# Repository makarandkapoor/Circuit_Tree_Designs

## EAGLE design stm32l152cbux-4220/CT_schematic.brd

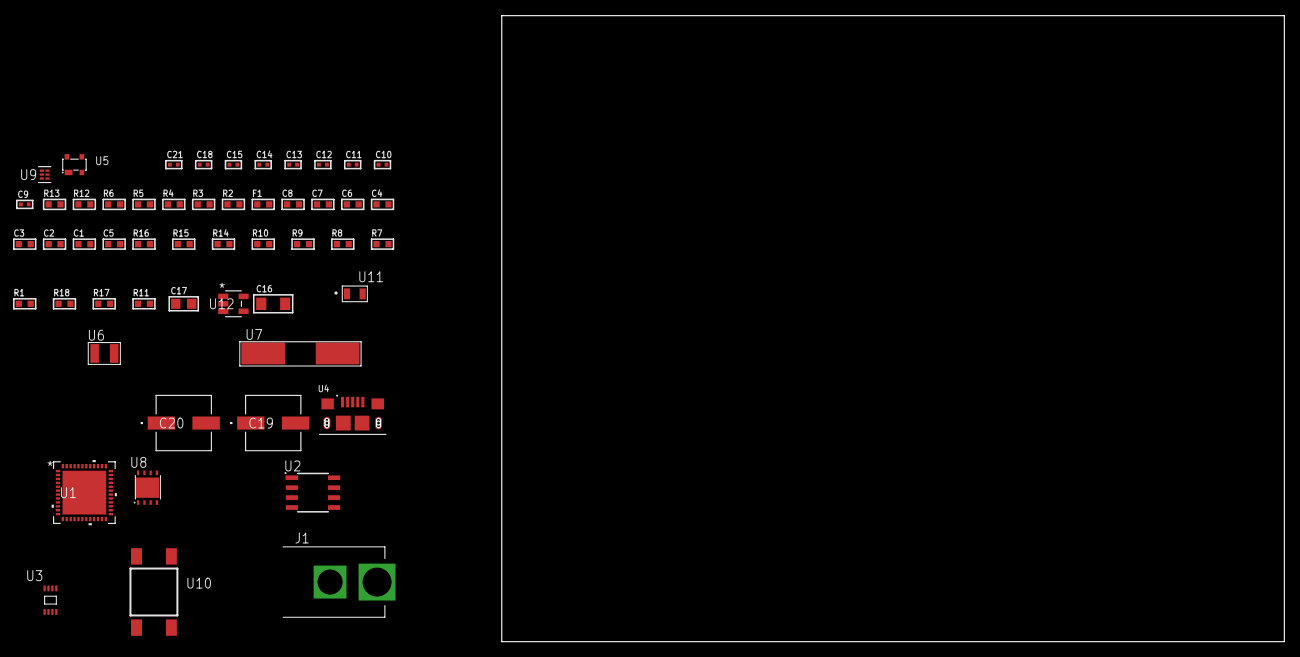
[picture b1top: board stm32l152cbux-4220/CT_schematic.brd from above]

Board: 2 copper layers, 122.6 x 80.0 mm, 53 parts (0 on the bottom side), 31 nets, no tracks yet.

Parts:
C1, C2, C3, C4, C6: 1e-07; C0603
C5: 4.7e-06; C0603
C7: 1e-08; C0603
C8: 1e-06; C0603
C9, C10, C11, C12: 1e-11; C0402
C13, C14, C15, C21: 1e-08; C0402
C16: 1e-05; C1206
C17: 1e-05; C0805
C18: 1e-07; C0402
C19, C20: 0.0001; EXV-9H
F1: 240.0; L0603
J1: PJ-037B; PJ-037B_PACKAGE
R1, R7, R8, R9, R10, R14, R15: 10000.0; R0603
R2, R13: 1000.0; R0603
R3: 910.0; R0603
R4: 4700.0; R0603
R5, R6: 2200.0; R0603
R11: 100000.0; R0603
R12: 806.0; R0603
R16: 82000.0; R0603
R17: 300000.0; R0603
R18: 120000.0; R0603
U1: STM32L152CBU6; UFQFPN48
U2: AT25128B-SSHL-T; SOIC-8
U3: 24AA16-I/MC; TDFN-8/6MM
U4: 10118193-0001LF; FCI_10118193-0001LF
U5: prtr5v0u2ax; SOT143B
U6: ABS07-32.768KHZ-7-T
U7: ABLS-25.000MHZ-B2F-T
U8: LP3878SDX-ADJ/NOPB; WSON-8
U9: TPS3895ADRYR; SON-6
U10: 4-1437565-2; SW_4-1437565-2
U11: Q65110A2395; LGM67K-G1J2-24-Z
U12: nc7sz125m5x; NC7SZ125M5X

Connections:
CLK_CRYSTAL_U1_3: C9.1, U1.3, U6.1
CLK_CRYSTAL_U1_4: C10.1, U1.4, U6.2
CLK_CRYSTAL_U1_5: C11.1, U1.5, U7.1
CLK_CRYSTAL_U1_6: C12.1, U1.6, U7.2
GND: C1.2, C2.2, C3.2, C4.2, C5.2, C6.2, C7.2, C8.2, C9.2, C10.2, C11.2, C12.2, C13.2, C14.2, C15.2, C16.2, C17.2, C18.2, C19.2, C20.2, C21.2, J1.2, R2.2, R7.2, R13.2, R16.2, R18.2, U1.8, U1.23, U1.35, U1.47, U1.49, U2.4, U3.4, U4.5, U4.6, U4.7, U4.8, U4.9, U5.1, U8.3, U8.PAD, U9.2, U11.C, U12.1, U12.3
NET_U1_1: C6.1, U1.1
NET_U1_7: R4.1, U1.7, U12.4
NET_U1_9: C7.1, C8.1, F1.1, U1.9
NET_U1_42: R5.1, U1.42, U3.6
NET_U1_43: R6.1, U1.43, U3.5
NET_U1_44: R7.1, U1.44
NET_U1_45: R3.1, U1.45, U11.A
NET_U1_46: R1.1, U1.46, U10.3, U10.4
NET_U2_3: R8.1, U2.3
NET_U2_7: R10.1, U2.7
NET_U5_4: U4.1, U5.4
NET_U8_1: C15.1, U8.1
NET_U8_6: R12.2, R13.1, U8.6
NET_U8_8: R11.1, U8.8
NET_U9_1: R15.1, R16.1, U9.1
NET_U9_3: R17.2, R18.1, U9.3
NET_U9_4: R14.1, U9.4, U12.2
NET_U10_1: R2.1, U10.1, U10.2
PROC_SPI1_MISO: U1.16, U2.2
PROC_SPI1_MOSI: U1.17, U2.5
PROC_SPI1_NSS: R9.1, U1.14, U2.1
PROC_SPI1_SCK: U1.15, U2.6
PROC_USB_DM: U1.32, U4.2, U5.3
PROC_USB_DP: U1.33, U4.3, U5.2
VCC_S1_9V1: C16.1, C19.1, C20.1, J1.1, R11.2, U8.4
VCC_TIER1_1V8: C1.1, C2.1, C3.1, C4.1, C5.1, C13.1, C14.1, C17.1, C18.1, C21.1, F1.2, R1.2, R3.2, R4.2, R5.2, R6.2, R8.2, R9.2, R10.2, R12.1, R14.2, R15.2, R17.1, U1.24, U1.36, U1.48, U2.8, U3.7, U3.8, U8.5, U9.6, U12.5

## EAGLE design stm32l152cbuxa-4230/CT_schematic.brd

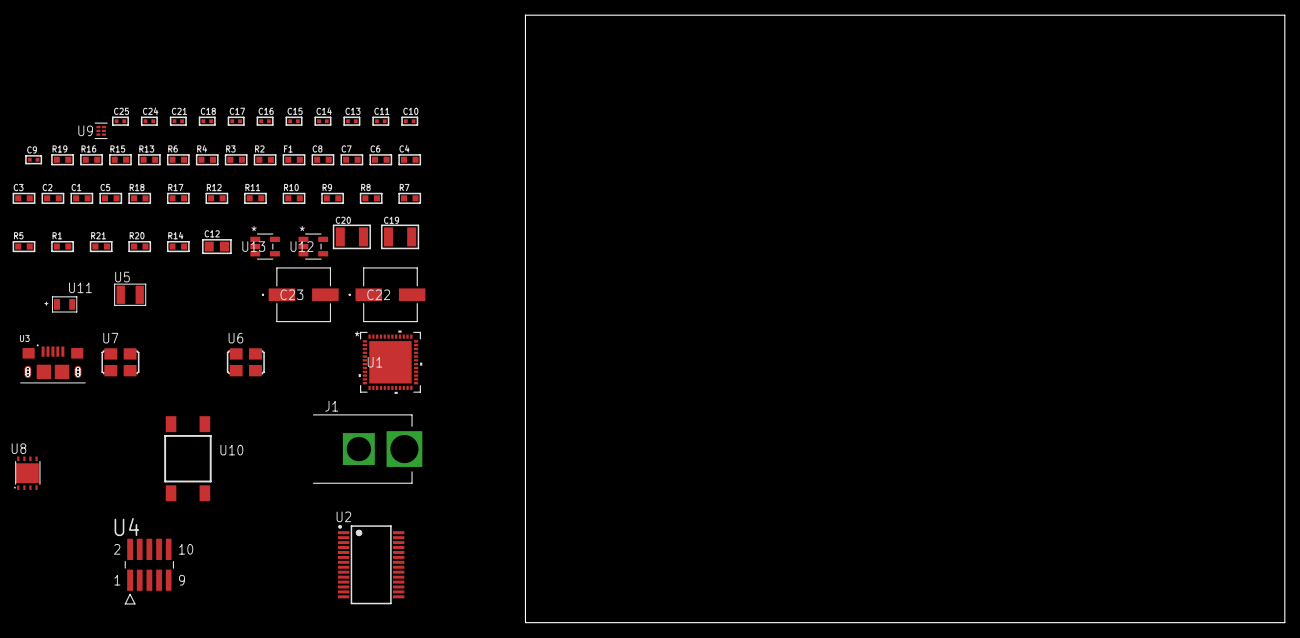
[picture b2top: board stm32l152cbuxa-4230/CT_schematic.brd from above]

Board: 2 copper layers, 165.8 x 80.0 mm, 61 parts (0 on the bottom side), 36 nets, no tracks yet.

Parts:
C1, C2, C3, C4, C6: 1e-07; C0603
C5: 4.7e-06; C0603
C7: 1e-08; C0603
C8: 1e-06; C0603
C9, C10: 1e-11; C0402
C11, C13, C14, C15, C21: 1e-07; C0402
C12: 4.7e-06; C0805
C16, C17, C18, C24, C25: 1e-08; C0402
C19, C20: 1e-05; C1210
C22, C23: 0.0001; EXV-9H
F1: 240.0; L0603
J1: PJ-037B; PJ-037B_PACKAGE
R1, R5, R7, R8, R9, R10, R11, R12, R17, R18: 10000.0; R0603
R2, R16: 1000.0; R0603
R3: 1600.5; R0603
R4, R6: 4700.0; R0603
R13: 5.0; R0603
R14: 100000.0; R0603
R15: 2231.0; R0603
R19: 9100.0; R0603
R20: 680000.0; R0603
R21: 120000.0; R0603
U1: STM32L152CBU6A; UFQFPN48
U2: FT232RL-REEL; SSOP-28
U3: 10118193-0001LF; FCI_10118193-0001LF
U4: FTSH-105-01-L-DV-K; SAMTEC_FTSH-105-01-L-DV-K
U5: ABS07-32.768KHZ-7-T
U6: ASFL1-12MHZ-NCS; ASFL1
U7: ASFL1-25MHZ-NCS; ASFL1
U8: LP3878SDX-ADJ/NOPB; WSON-8
U9: TPS3895ADRYR; SON-6
U10: 4-1437565-2; SW_4-1437565-2
U11: Q65110A2395; LGM67K-G1J2-24-Z
U12, U13: nc7sz125m5x; NC7SZ125M5X

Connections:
CLK_CRYSTAL_U1_3: C9.1, U1.3, U5.1
CLK_CRYSTAL_U1_4: C10.1, U1.4, U5.2
CLK_U1_5: U1.5, U7.3
CLK_U2_27: U2.27, U6.3
GND: C1.2, C2.2, C3.2, C4.2, C5.2, C6.2, C7.2, C8.2, C9.2, C10.2, C11.2, C12.2, C13.2, C14.2, C15.2, C16.2, C17.2, C18.2, C19.2, C20.2, C21.2, C22.2, C23.2, C24.2, C25.2, J1.2, R2.2, R5.2, R8.2, R12.2, R13.2, R16.2, R19.2, R21.2, U1.8, U1.23, U1.35, U1.47, U1.49, U2.7, U2.18, U2.21, U2.25, U2.26, U3.5, U3.6, U3.7, U3.8, U3.9, U4.3, U4.5, U6.2, U7.2, U8.3, U8.PAD, U9.2, U11.C, U12.2, U12.3, U13.1, U13.3
NET_U1_1: C6.1, U1.1
NET_U1_7: R4.1, U1.7, U13.4
NET_U1_9: C7.1, C8.1, F1.1, U1.9
NET_U1_44: R5.1, U1.44
NET_U1_45: R3.1, U1.45, U11.A
NET_U1_46: R1.1, U1.46, U10.3, U10.4
NET_U2_14: R7.1, U2.14
NET_U2_17: C13.1, U2.17
NET_U2_19: R8.1, U2.19
NET_U3_1: R6.1, U3.1
NET_U3_2: U2.16, U3.2
NET_U3_3: U2.15, U3.3
NET_U4_9: R13.1, U4.9
NET_U8_1: C18.1, U8.1
NET_U8_6: R15.2, R16.1, U8.6
NET_U8_8: R14.1, U8.8
NET_U9_1: R18.1, R19.1, U9.1
NET_U9_3: R20.2, R21.1, U9.3
NET_U9_4: R17.1, U9.4, U12.4, U13.2
NET_U10_1: R2.1, U10.1, U10.2
PROC_SYS_JTCK_SWCLK: R12.1, U1.37, U4.4
PROC_SYS_JTDI: R10.1, U1.38, U4.8
PROC_SYS_JTDO_TRACESWO: U1.39, U4.6
PROC_SYS_JTMS_SWDIO: R11.1, U1.34, U4.2
PROC_USART1_CTS: U1.32, U2.3
PROC_USART1_RTS: U1.33, U2.11
PROC_USART1_RX: U1.31, U2.1
PROC_USART1_TX: U1.30, U2.5
RST_OUT_U4_JTAG_RST_B: R9.1, U4.10, U12.1
VCC_S1_15V1: C19.1, C22.1, C23.1, J1.1, R14.2, U8.4
VCC_TIER1_3V3: C1.1, C2.1, C3.1, C4.1, C5.1, C11.1, C12.1, C14.1, C15.1, C16.1, C17.1, C20.1, C21.1, C24.1, C25.1, F1.2, R1.2, R3.2, R4.2, R7.2, R9.2, R10.2, R11.2, R15.1, R17.2, R18.2, R20.1, U1.24, U1.36, U1.48, U2.4, U2.20, U4.1, U6.4, U7.4, U8.5, U9.6, U12.5, U13.5

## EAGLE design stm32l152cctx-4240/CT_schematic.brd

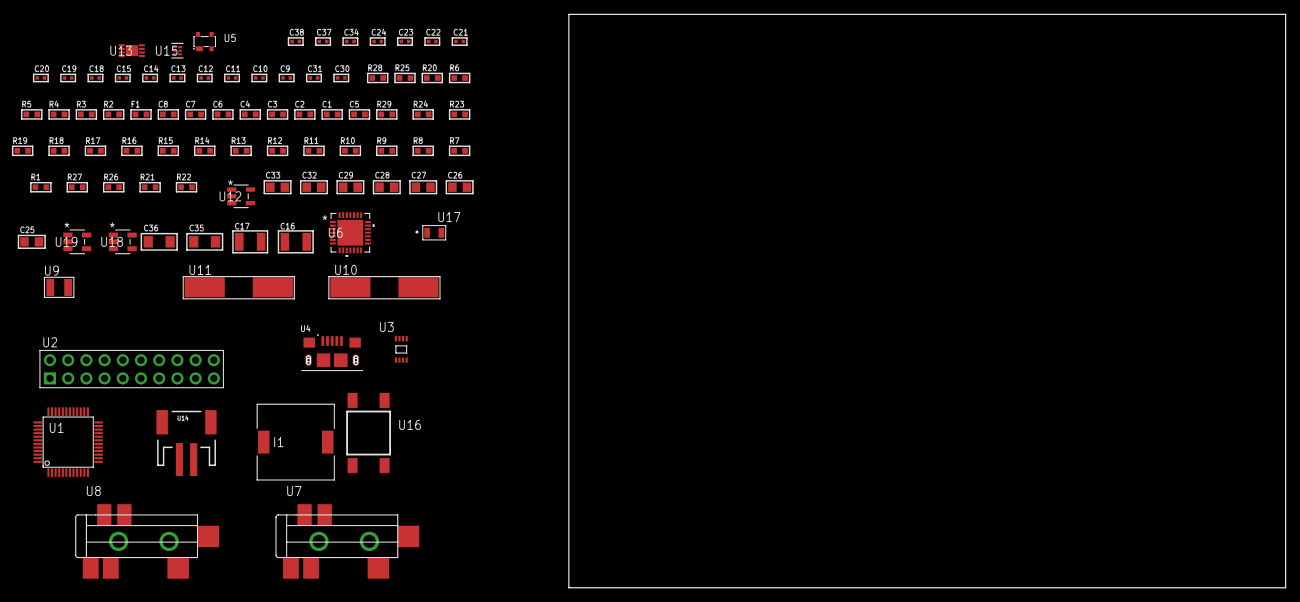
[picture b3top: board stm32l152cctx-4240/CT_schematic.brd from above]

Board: 2 copper layers, 88 parts (0 on the bottom side), 46 nets, no tracks yet.

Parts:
C1, C2, C3, C4, C6: 1e-07; C0603
C5: 4.7e-06; C0603
C7: 1e-08; C0603
C8: 1e-06; C0603
C9, C10, C11, C12: 1e-11; C0402
C13, C14, C20, C21, C22, C23, C24, C34: 1e-07; C0402
C15, C37, C38: 1e-08; C0402
C16, C17: 2.2e-05; C1210
C18, C19: 1e-09; C0402
C25, C26, C27, C28, C29, C32, C33: 1e-05; C0805
C30, C31: 2.2e-11; C0402
C35, C36: 1e-05; C1206
F1: 240.0; L0603
I1: 3.8e-06; DR1040
R1, R7, R8, R9, R10, R11, R12, R13, R14, R15, R16, R23, R24, R29: 10000.0; R0603
R2: 1000.0; R0603
R3: 1600.5; R0603
R4: 4700.0; R0603
R5, R6: 2200.0; R0603
R17, R18, R19: 47000.0; R0603
R20: 680.0; R0603
R21: 220000.0; R0603
R22: 1000000.0; R0603
R25: 9100.0; R0603
R26: 680000.0; R0603
R27: 120000.0; R0603
R28: 2000.0; R0603
U1: STM32L152CCT6; LQFP48
U2: TST-110-05-T-D-RA
U3: 24AA64T-I/MNY; TDFN-8/6MM
U4: 10118193-0001LF; FCI_10118193-0001LF
U5: prtr5v0u2ax; SOT143B
U6: WM8731CLSEFL; QFN-28
U7, U8: SJ-43515TS-SMT-TR
U9: ABS07-32.768KHZ-7-T
U10: ABLS-25.000MHZ-B2F-T
U11: ABLS-12.288MHZ-B4-T
U12: ltc3406es5; TSOT-23-5
U13: MCP73831T-2ACI/MC; DFN8_2X3MC
U14: S2B-PH-SM4-TB(LF)(SN); JST-2-SMD
U15: TPS3895ADRYR; SON-6
U16: 4-1437565-2; SW_4-1437565-2
U17: Q65110A2395; LGM67K-G1J2-24-Z
U18, U19: nc7sz125m5x; NC7SZ125M5X

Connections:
CLK_CRYSTAL_U1_3: C9.1, U1.3, U9.1
CLK_CRYSTAL_U1_4: C10.1, U1.4, U9.2
CLK_CRYSTAL_U1_5: C11.1, U1.5, U10.1
CLK_CRYSTAL_U1_6: C12.1, U1.6, U10.2
CLK_CRYSTAL_U6_1: C30.1, U6.1, U11.1
CLK_CRYSTAL_U6_2: C31.1, U6.2, U11.2
GND: C1.2, C2.2, C3.2, C4.2, C5.2, C6.2, C7.2, C8.2, C9.2, C10.2, C11.2, C12.2, C13.2, C14.2, C15.2, C19.2, C20.2, C21.2, C22.2, C23.2, C24.2, C25.2, C26.2, C27.2, C28.2, C29.2, C30.2, C31.2, C32.2, C33.1, C33.2, C34.2, C35.2, C36.2, C37.2, C38.2, R2.2, R7.2, R13.2, R15.2, R16.2, R17.2, R18.2, R19.2, R21.2, R25.2, R27.2, R28.2, U1.8, U1.23, U1.35, U1.47, U2.4, U2.6, U2.8, U2.10, U2.12, U2.14, U2.16, U2.18, U2.20, U3.4, U4.5, U4.6, U4.7, U4.8, U4.9, U5.1, U6.4, U6.15, U6.19, U6.25, U6.26, U6.29, U7.1, U8.1, U12.2, U13.6, U13.9, U14.2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
INPUT_USBPOWER_5V: C35.1, R29.2, U4.1, U5.4, U13.1, U13.2
NET_U1_1: C6.1, U1.1
NET_U1_7: R4.1, U1.7, U19.4
NET_U1_9: C7.1, C8.1, F1.1, U1.9
NET_U1_42: R5.1, U1.42, U3.6
NET_U1_43: R6.1, U1.43, U3.5
NET_U1_44: R7.1, U1.44
NET_U1_45: R3.1, U1.45, U17.A
NET_U1_46: R1.1, U1.46, U16.3, U16.4
NET_U2_19: R13.1, U2.19
NET_U3_1: R14.1, U3.1
NET_U3_2: R15.1, U3.2
NET_U3_3: R16.1, U3.3
NET_U6_20: C24.1, C29.1, U6.20
NET_U7_2: C17.1, R18.1, U7.2
NET_U7_5: C16.1, R17.1, U7.5
NET_U8_5: C18.1, C19.1, R19.1, R20.1, U8.5
NET_U12_3: I1.1, U12.3
NET_U12_5: R21.1, R22.1, U12.5
NET_U12_ATNET_3: I1.2, R22.2
NET_U13_5: R29.1, U13.5
NET_U13_8: R28.1, U13.8
NET_U15_1: R24.1, R25.1, U15.1
NET_U15_3: R26.2, R27.1, U15.3
NET_U15_4: R23.1, U15.4, U18.4, U19.2
NET_U16_1: R2.1, U16.1, U16.2
PROC_I2S2_CK: U1.26, U6.7
PROC_I2S2_SD: U1.28, U6.8
PROC_I2S2_WS: U1.25, U6.9, U6.11
PROC_SYS_JTCK_SWCLK: R11.1, U1.37, U2.9
PROC_SYS_JTDI: R9.1, U1.38, U2.5
PROC_SYS_JTDO_TRACESWO: U1.39, U2.13
PROC_SYS_JTMS_SWDIO: R10.1, U1.34, U2.7
PROC_SYS_JTRST: R8.1, U1.40, U2.3
PROC_USB_DM: U1.32, U4.2, U5.3
PROC_USB_DP: U1.33, U4.3, U5.2
RST_OUT_U2_SRESET_B: R12.1, U2.15, U18.1
VCC_S1_3V7: C32.1, C36.1, U12.4, U13.3, U13.4, U14.1
VCC_TIER1_3V3: C1.1, C2.1, C3.1, C4.1, C5.1, C13.1, C14.1, C15.1, C20.1, C21.1, C22.1, C23.1, C25.1, C26.1, C27.1, C28.1, C33.2, C34.1, C37.1, C38.1, F1.2, I1.2, R1.2, R3.2, R4.2, R5.2, R6.2, R8.2, R9.2, R10.2, R11.2, R12.2, R14.2, R22.2, R23.2, R24.2, R26.1, U1.24, U1.36, U1.48, U2.1, U2.2, U3.7, U3.8, U6.3, U6.5, U6.12, U6.18, U15.6, U18.5, U19.5

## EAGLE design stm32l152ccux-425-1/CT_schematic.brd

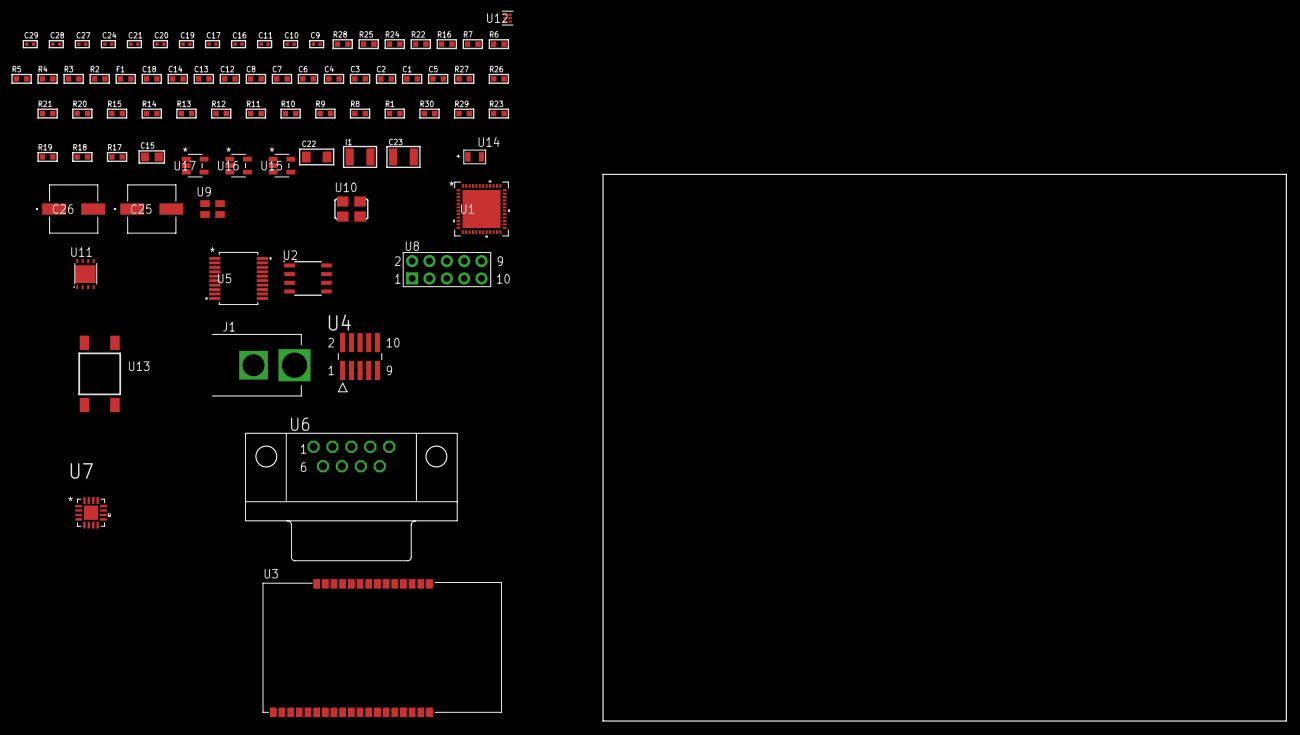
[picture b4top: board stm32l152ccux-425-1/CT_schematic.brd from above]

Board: 2 copper layers, 100.0 x 80.0 mm, 79 parts (0 on the bottom side), 60 nets, no tracks yet.

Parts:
C1, C2, C3, C4, C6: 1e-07; C0603
C5: 4.7e-06; C0603
C7: 1e-08; C0603
C8, C12, C13, C14, C18: 1e-06; C0603
C9, C19, C20, C21, C27, C28, C29: 1e-08; C0402
C10, C11, C16, C17, C24: 1e-07; C0402
C15: 4.7e-06; C0805
C22: 1e-05; C1206
C23: 1e-05; C1210
C25, C26: 0.0001; EXV-9H
F1: 240.0; L0603
I1: 1.5e-05; L1210
J1: PJ-037B; PJ-037B_PACKAGE
R1, R8, R9, R10, R11, R12, R13, R14, R15, R20, R21, R26, R27: 10000.0; R0603
R2, R25: 1000.0; R0603
R3: 1600.5; R0603
R4, R5: 4700.0; R0603
R6, R7: 2200.0; R0603
R16: 5.0; R0603
R17, R18, R19, R23: 100000.0; R0603
R22: 47.0; R0603
R24: 2231.0; R0603
R28: 9100.0; R0603
R29: 680000.0; R0603
R30: 120000.0; R0603
U1: STM32L152CCU6; UFQFPN48
U2: AT25256B-SSHL-T; SOIC-8
U3: ETRX3587
U4: FTSH-105-01-L-DV-K; SAMTEC_FTSH-105-01-L-DV-K
U5: MAX3218EAP+T; SSOP-20
U6: 182-009-113R531; 182-009-MALE
U7: TSC2013QRSARQ1; QFN65P400X400X100-17N
U8: HTSS-105-01-G-D
U9: ASEK-32.768KHz-ECST; ASEK
U10: ASFL1-25MHZ-NCS; ASFL1
U11: LP3878SDX-ADJ/NOPB; WSON-8
U12: TPS3895ADRYR; SON-6
U13: 4-1437565-2; SW_4-1437565-2
U14: Q65110A2395; LGM67K-G1J2-24-Z
U15, U16, U17: nc7sz125m5x; NC7SZ125M5X

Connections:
CLK_U1_3: U1.3, U9.3
CLK_U1_5: U1.5, U10.3
GND: C1.2, C2.2, C3.2, C4.2, C5.2, C6.2, C7.2, C8.2, C9.2, C10.2, C11.2, C12.2, C13.2, C14.2, C19.2, C20.2, C21.2, C22.2, C23.2, C24.2, C25.2, C26.2, C27.2, C28.2, C29.2, J1.2, R2.2, R8.2, R12.2, R16.2, R25.2, R28.2, R30.2, U1.8, U1.23, U1.35, U1.47, U1.49, U2.4, U3.1, U3.13, U3.19, U3.20, U3.31, U3.33, U4.3, U4.5, U5.5, U5.17, U5.20, U6.5, U7.17, U8.9, U9.2, U10.2, U11.3, U11.PAD, U12.2, U14.C, U15.2, U15.3, U16.1, U16.3, U17.1, U17.3
NET_U1_1: C6.1, U1.1
NET_U1_7: R5.1, U1.7, U17.4
NET_U1_9: C7.1, C8.1, F1.1, U1.9
NET_U1_43: R7.1, U1.43, U7.1
NET_U1_44: R8.1, U1.44
NET_U1_45: R3.1, U1.45, U14.A
NET_U1_46: R1.1, U1.46, U13.3, U13.4
NET_U2_3: R9.1, U2.3
NET_U2_7: R11.1, U2.7
NET_U3_7: R4.1, U3.7, U16.4
NET_U3_21: R12.1, U3.21
NET_U4_9: R16.1, U4.9
NET_U5_1: I1.1, U5.1
NET_U5_2: R17.1, U5.2
NET_U5_3: R18.1, U5.3
NET_U5_4: R19.1, U5.4
NET_U5_15: C14.1, U5.15
NET_U5_16: C15.2, U5.16
NET_U5_18: C15.1, U5.18
NET_U5_19: C13.1, U5.19
NET_U6_2: U5.12, U6.2
NET_U6_3: U5.14, U6.3
NET_U6_7: U5.11, U6.7
NET_U6_8: U5.13, U6.8
NET_U7_4: R21.1, U7.4
NET_U7_5: R20.1, U7.5
NET_U7_9: C16.2, C17.2, C18.2, R22.2, U7.9
NET_U7_15: R22.1, U7.8, U7.15
NET_U8_3: U7.12, U8.3
NET_U8_4: U7.14, U8.4
NET_U8_5: U7.11, U8.5
NET_U8_6: U7.13, U8.6
NET_U11_1: C21.1, U11.1
NET_U11_6: R24.2, R25.1, U11.6
NET_U11_8: R23.1, U11.8
NET_U12_1: R27.1, R28.1, U12.1
NET_U12_3: R29.2, R30.1, U12.3
NET_U12_4: R26.1, U12.4, U15.4, U16.2, U17.2
NET_U13_1: R2.1, U13.1, U13.2
PROC_SPI1_MISO: U1.16, U2.2
PROC_SPI1_MOSI: U1.17, U2.5
PROC_SPI1_NSS: R10.1, U1.14, U2.1
PROC_SPI1_SCK: U1.15, U2.6
PROC_SYS_JTCK_SWCLK: R14.1, U1.37, U4.4
PROC_SYS_JTDO_TRACESWO: U1.39, U4.6
PROC_SYS_JTMS_SWDIO: R15.1, U1.34, U4.2
PROC_USART1_CTS: U1.32, U3.8
PROC_USART1_RTS: U1.33, U3.6
PROC_USART1_RX: U1.31, U3.17
PROC_USART1_TX: U1.30, U3.18
PROC_USART2_CTS: U1.10, U5.8
PROC_USART2_RTS: U1.11, U5.10
PROC_USART2_RX: U1.13, U5.9
PROC_USART2_TX: U1.12, U5.7
RST_OUT_U4_JTAG_RST_B: R13.1, U4.10, U15.1
VCC_S1_9V7: C22.1, C25.1, C26.1, J1.1, R23.2, U11.4
VCC_TIER1_3V3: C1.1, C2.1, C3.1, C4.1, C5.1, C9.1, C10.1, C11.1, C12.1, C16.1, C17.1, C18.1, C19.1, C20.1, C23.1, C24.1, C27.1, C28.1, C29.1, F1.2, I1.2, R1.2, R3.2, R4.2, R5.2, R6.2, R7.2, R9.2, R10.2, R11.2, R13.2, R14.2, R15.2, R17.2, R18.2, R19.2, R20.2, R21.2, R24.1, R26.2, R27.2, R29.1, U1.24, U1.36, U1.48, U2.8, U3.32, U4.1, U5.6, U7.7, U7.10, U9.4, U10.4, U11.5, U12.6, U15.5, U16.5, U17.5

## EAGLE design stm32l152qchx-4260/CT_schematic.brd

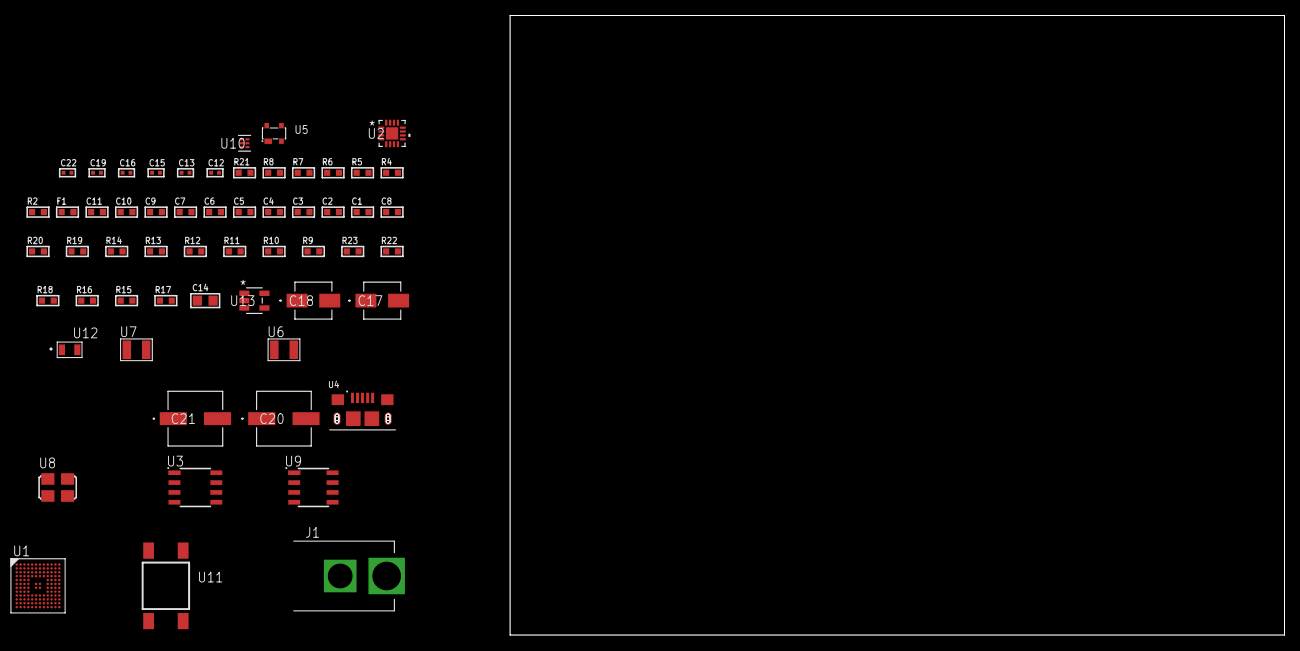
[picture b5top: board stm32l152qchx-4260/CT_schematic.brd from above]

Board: 2 copper layers, 122.6 x 80.0 mm, 58 parts (0 on the bottom side), 32 nets, no tracks yet.

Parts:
C1, C2, C3, C4, C5, C6, C7, C9: 1e-07; C0603
C8: 4.7e-06; C0603
C10: 1e-08; C0603
C11: 1e-06; C0603
C12, C13: 1e-11; C0402
C14: 4.7e-06; C0805
C15, C16, C22: 1e-08; C0402
C17: 1e-06; EXV-9B
C18: 2.2e-06; EXV-9B
C19: 1e-07; C0402
C20, C21: 0.0001; EXV-9H
F1: 240.0; L0603
J1: PJ-037B; PJ-037B_PACKAGE
R2: 1000.0; R0603
R4: 4700.0; R0603
R5, R6, R7, R8: 2200.0; R0603
R9, R10, R11, R12, R13, R14, R19, R20: 10000.0; R0603
R15, R16, R18: 100000.0; R0603
R17: 164658.62; R0603
R21: 9100.0; R0603
R22: 680000.0; R0603
R23: 120000.0; R0603
U1: STM32L152QCH6; UFBGA132
U2: M41T65Q6F; M41T65_QFN-16
U3: 24AA1025T-I/SN; SOIC-8
U4: 10118193-0001LF; FCI_10118193-0001LF
U5: prtr5v0u2ax; SOT143B
U6, U7: ABS07-32.768KHZ-7-T
U8: ASFL1-25MHZ-NCS; ASFL1
U9: LP2954AIMX/NOPB; LP2954
U10: TPS3895ADRYR; SON-6
U11: 4-1437565-2; SW_4-1437565-2
U12: Q65110A2395; LGM67K-G1J2-24-Z
U13: nc7sz125m5x; NC7SZ125M5X

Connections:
CLK_CRYSTAL_U1_D1: C12.1, U1.D1, U7.1
CLK_CRYSTAL_U1_E1: C13.1, U1.E1, U7.2
CLK_CRYSTAL_U2_1: U2.1, U6.1
CLK_CRYSTAL_U2_2: U2.2, U6.2
CLK_U1_F1: U1.F1, U8.3
GND: C1.2, C2.2, C3.2, C4.2, C5.2, C6.2, C7.2, C8.2, C9.2, C10.2, C11.2, C12.2, C13.2, C14.2, C15.2, C16.2, C17.2, C18.2, C19.2, C20.2, C21.2, C22.2, J1.2, R2.2, R9.2, R14.2, R18.2, R21.2, R23.2, U1.D3, U1.E3, U1.F2, U1.F6, U1.F7, U1.F11, U1.F12, U1.J1, U2.3, U2.5, U2.17, U3.4, U3.7, U4.5, U4.6, U4.7, U4.8, U4.9, U5.1, U8.2, U9.4, U10.2, U12.C, U13.1, U13.3
NET_U1_A3: R5.1, U1.A3, U2.10
NET_U1_A4: R9.1, U1.A4
NET_U1_B3: R6.1, U1.B3, U2.9
NET_U1_E2: C9.1, U1.E2
NET_U1_H2: R4.1, U1.H2, U13.4
NET_U1_L10: R7.1, U1.L10, U3.6
NET_U1_L11: R8.1, U1.L11, U3.5
NET_U1_M1: C10.1, C11.1, F1.1, U1.L1, U1.M1
NET_U1_M12: U11.3, U11.4
NET_U2_4: R10.1, U2.4
NET_U2_11: R11.1, U2.11
NET_U3_1: R13.1, U3.1
NET_U3_2: R14.1, U3.2
NET_U3_3: R12.1, U3.3
NET_U5_4: U4.1, U5.4
NET_U9_3: R16.1, U9.3
NET_U9_5: R15.1, U9.5
NET_U9_7: R17.2, R18.1, U9.7
NET_U10_1: R20.1, R21.1, U10.1
NET_U10_3: R22.2, R23.1, U10.3
NET_U10_4: R19.1, U10.4, U13.2
NET_U11_1: R2.1, U11.1, U11.2
PROC_USB_DM: U1.B12, U4.2, U5.3
PROC_USB_DP: U1.A12, U4.3, U5.2
VCC_S1_14V3: C17.1, C20.1, C21.1, J1.1, R16.2, U9.8
VCC_TIER1_3V3: C1.1, C2.1, C3.1, C4.1, C5.1, C6.1, C7.1, C8.1, C14.1, C15.1, C16.1, C18.1, C19.1, C22.1, F1.2, R4.2, R5.2, R6.2, R7.2, R8.2, R10.2, R11.2, R12.2, R13.2, R15.2, R17.1, R19.2, R20.2, R22.1, U1.C4, U1.G2, U1.G6, U1.G7, U1.G11, U1.G12, U1.H3, U2.14, U3.8, U8.4, U9.1, U10.6, U13.5

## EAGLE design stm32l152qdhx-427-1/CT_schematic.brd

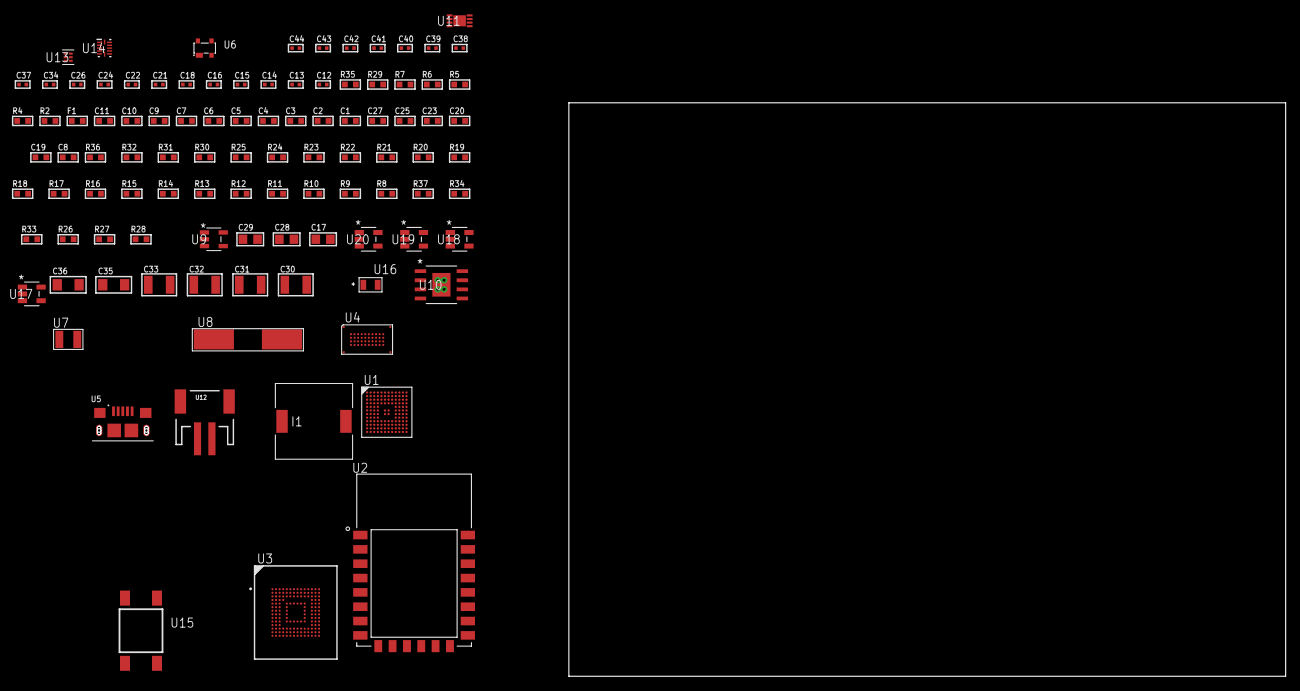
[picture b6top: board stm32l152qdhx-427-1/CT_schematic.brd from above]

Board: 2 copper layers, 101 parts (0 on the bottom side), 76 nets, no tracks yet.

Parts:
C1, C2, C3, C4, C5, C6, C7, C9: 1e-07; C0603
C8: 4.7e-06; C0603
C10: 1e-08; C0603
C11: 1e-06; C0603
C12, C13, C14, C15: 1e-11; C0402
C16, C18, C21, C22, C24, C26, C34, C38, C40: 1e-07; C0402
C17, C28, C29: 1e-05; C0805
C19, C20, C23, C25, C27: 2.2e-06; C0603
C30, C31, C32, C33: 1e-05; C1210
C35, C36: 1e-05; C1206
C37, C39, C41, C42, C43, C44: 1e-08; C0402
F1: 240.0; L0603
I1: 3.8e-06; DR1040
R2: 1000.0; R0603
R4, R5, R6, R7: 4700.0; R0603
R8, R9, R10, R11, R22, R23, R24, R25, R30, R31, R36: 10000.0; R0603
R12, R13, R14, R15, R16, R17, R18, R19, R20, R21: 34000.0; R0603
R26: 490000.0; R0603
R27: 1000000.0; R0603
R28: 4031.5447154472; R0603
R29: 2200.0; R0603
R32: 82000.0; R0603
R33: 300000.0; R0603
R34: 120000.0; R0603
R35: 2000.0; R0603
R37: 200000.0; R0603
U1: STM32L152QDH6; UFBGA132
U2: ESP8266-12E
U3: mtfc4gmcdm; TFBGA-153
U4: S29VS256RABBHW000
U5: 10118193-0001LF; FCI_10118193-0001LF
U6: prtr5v0u2ax; SOT143B
U7: ABS07-32.768KHZ-7-T
U8: ABLS-25.000MHZ-B2F-T
U9: ltc3406es5; TSOT-23-5
U10: MIC5234YME; SOIC-8_EP
U11: MCP73831T-2ACI/MC; DFN8_2X3MC
U12: S2B-PH-SM4-TB(LF)(SN); JST-2-SMD
U13: TPS3895ADRYR; SON-6
U14: LSF0204DRUTR; RUT0012A
U15: 4-1437565-2; SW_4-1437565-2
U16: Q65110A2395; LGM67K-G1J2-24-Z
U17, U18, U19, U20: nc7sz125m5x; NC7SZ125M5X

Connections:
CLK_CRYSTAL_U1_D1: C12.1, U1.D1, U7.1
CLK_CRYSTAL_U1_E1: C13.1, U1.E1, U7.2
CLK_CRYSTAL_U1_F1: C14.1, U1.F1, U8.1
CLK_CRYSTAL_U1_G1: C15.1, U1.G1, U8.2
GND: C1.2, C2.2, C3.2, C4.2, C5.2, C6.2, C7.2, C8.2, C9.2, C10.2, C11.2, C12.2, C13.2, C14.2, C15.2, C16.2, C17.2, C18.2, C19.2, C20.2, C21.2, C22.2, C23.2, C24.2, C25.2, C26.2, C27.2, C28.2, C29.1, C29.2, C30.2, C31.2, C32.2, C33.2, C34.2, C35.2, C36.2, C37.2, C38.2, C39.2, C40.2, C41.2, C42.2, C43.2, C44.2, R2.2, R8.2, R11.2, R26.2, R29.2, R32.2, R34.2, R35.2, U1.D3, U1.E3, U1.F2, U1.F6, U1.F7, U1.F11, U1.F12, U1.J1, U2.15, U3.C4, U3.E7, U3.G5, U3.H10, U3.K8, U3.N2, U3.N5, U3.P4, U3.P6, U4.C5, U4.D12, U4.E3, U4.F5, U5.5, U5.6, U5.7, U5.8, U5.9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
INPUT_USBPOWER_5V: C35.1, R36.2, U5.1, U6.4, U11.1, U11.2
NET_U1_A4: R8.1, U1.A4
NET_U1_E2: C9.1, U1.E2
NET_U1_H2: R7.1, U1.H2, U20.4
NET_U1_M1: C10.1, C11.1, F1.1, U1.L1, U1.M1
NET_U1_M6: U15.3, U15.4
NET_U2_1: R6.1, U2.1, U19.4
NET_U2_3: R9.1, U2.3
NET_U2_18: R10.1, U2.18
NET_U3_C2: C20.1, C21.1, U3.C2
NET_U3_K5: R4.1, U3.K5, U17.4
NET_U4_D8: R5.1, U4.D8, U18.4
NET_U9_3: I1.1, U9.3
NET_U9_5: R26.1, R27.1, U9.5
NET_U9_ATNET_3: I1.2, R27.2
NET_U10_4: R28.2, R29.1, U10.4
NET_U11_5: R36.1, U11.5
NET_U11_8: R35.1, U11.8
NET_U13_1: R31.1, R32.1, U13.1
NET_U13_3: R33.2, R34.1, U13.3
NET_U13_4: R30.1, U13.4, U17.2, U18.2, U19.2, U20.2
NET_U14_12: R37.1, U14.12
NET_U15_1: R2.1, U15.1, U15.2
PROC_FSMC_A16: U1.J11, U4.D4
PROC_FSMC_A17: U1.J10, U4.C11
PROC_FSMC_A18: U1.H12, U4.D10
PROC_FSMC_A19: U1.A1, U4.C10
PROC_FSMC_A20: U1.B1, U4.D5
PROC_FSMC_A21: U1.C2, U4.C4
PROC_FSMC_A23: U1.B2, U4.D7
PROC_FSMC_CLK: U1.B8, U4.C6
PROC_FSMC_D0: U1.H11, U4.F3
PROC_FSMC_D1: U1.H10, U4.F4
PROC_FSMC_D2: U1.C9, U4.E6
PROC_FSMC_D3: U1.B9, U4.E7
PROC_FSMC_D4: U1.M7, U4.F8
PROC_FSMC_D5: U1.L7, U4.F9
PROC_FSMC_D6: U1.M8, U4.E10
PROC_FSMC_D7: U1.L8, U4.E11
PROC_FSMC_D8: U1.M9, U4.E4
PROC_FSMC_D9: U1.L9, U4.E5
PROC_FSMC_D10: U1.M10, U4.F6
PROC_FSMC_D11: U1.M11, U4.F7
PROC_FSMC_D12: U1.M12, U4.E8
PROC_FSMC_D13: U1.K9, U4.E9
PROC_FSMC_D14: U1.K8, U4.F11
PROC_FSMC_D15: U1.J12, U4.F12
PROC_FSMC_NE2: R23.1, U1.D9, U4.D11
PROC_FSMC_NL: U1.B4, U4.D6
PROC_FSMC_NOE: R25.1, U1.B7, U4.E12
PROC_FSMC_NWAIT: R22.1, U1.B6, U4.C3
PROC_FSMC_NWE: R24.1, U1.A6, U4.C8
PROC_SDIO_CK: R21.1, U1.B10, U3.M6
PROC_SDIO_CMD: R20.1, U1.C8, U3.M5
PROC_SDIO_D0: R12.1, U1.E10, U3.A3
PROC_SDIO_D1: R13.1, U1.D12, U3.A4
PROC_SDIO_D2: R14.1, U1.B11, U3.A5
PROC_SDIO_D3: R15.1, U1.C10, U3.B2
PROC_SDIO_D4: R16.1, U1.A3, U3.B3
PROC_SDIO_D5: R17.1, U1.B3, U3.B4
PROC_SDIO_D6: R18.1, U1.E12, U3.B5
PROC_SDIO_D7: R19.1, U1.E11, U3.B6
PROC_SPI1_MISO_TOXCVR: U2.6, U14.9
PROC_SPI1_MOSI_TOXCVR: U2.7, U14.10
PROC_SPI1_NSS_TOXCVR: R11.1, U2.16, U14.7
PROC_SPI1_SCK_TOXCVR: U2.5, U14.8
PROC_USB_DM: U1.B12, U5.2, U6.3
PROC_USB_DP: U1.A12, U5.3, U6.2
VCC_S1_3V7: C28.1, C30.1, C31.1, C36.1, U9.4, U10.5, U10.8, U11.3, U11.4, U12.1
VCC_TIER1_1V8: C1.1, C2.1, C3.1, C4.1, C5.1, C6.1, C7.1, C8.1, C18.1, C19.1, C24.1, C25.1, C26.1, C27.1, C29.2, C34.1, C39.1, C40.1, C41.1, C42.1, C43.1, C44.1, F1.2, I1.2, R4.2, R5.2, R7.2, R12.2, R13.2, R14.2, R15.2, R16.2, R17.2, R18.2, R19.2, R20.2, R21.2, R22.2, R23.2, R24.2, R25.2, R27.2, R30.2, R31.2, R33.1, R37.2, U1.C4, U1.G2, U1.G6, U1.G7, U1.G11, U1.G12, U1.H3, U3.C6, U3.M4, U3.N4, U3.P3, U3.P5, U4.C7, U4.D3, U4.F10, U13.6, U14.1, U17.5, U18.5, U19.5, U20.5
VCC_TIER1_3V3: C16.1, C17.1, C22.1, C23.1, C32.1, C33.1, C37.1, C38.1, R6.2, R9.2, R10.2, R28.1, U2.8, U3.E6, U3.F5, U3.J10, U3.K9, U10.1, U14.11

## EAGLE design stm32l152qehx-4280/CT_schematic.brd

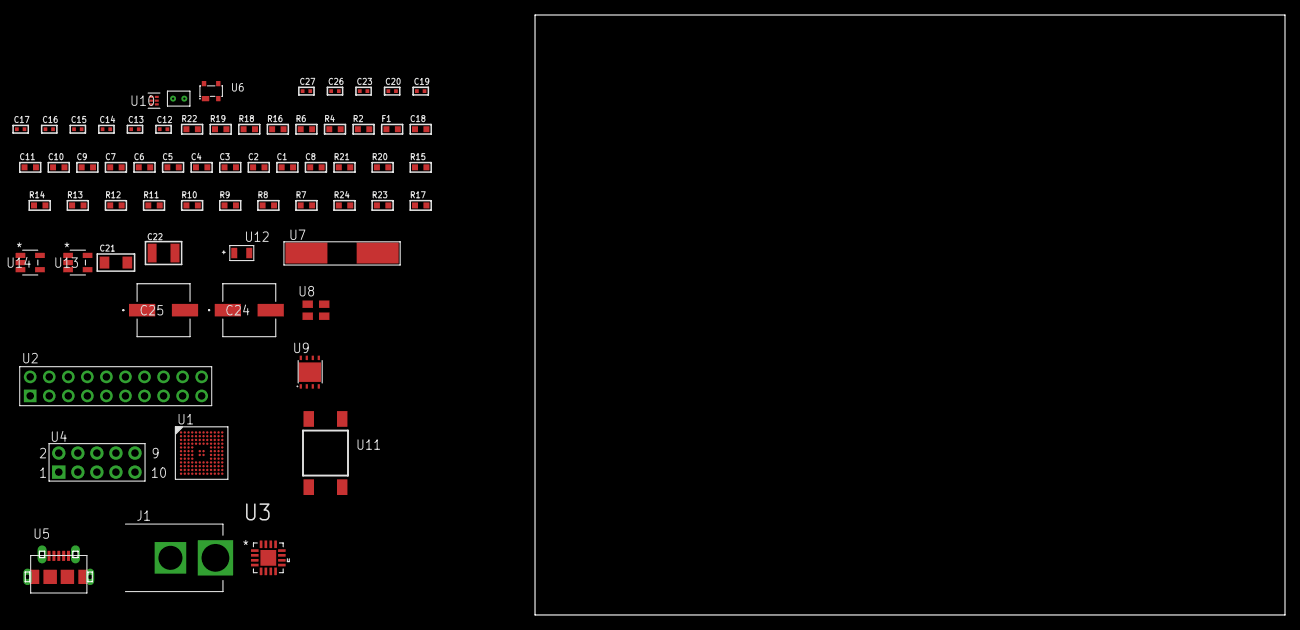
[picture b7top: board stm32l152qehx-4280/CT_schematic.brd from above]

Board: 2 copper layers, 168.0 x 80.0 mm, 65 parts (0 on the bottom side), 38 nets, no tracks yet.

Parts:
C1, C2, C3, C4, C5, C6, C7, C9: 1e-07; C0603
C8: 4.7e-06; C0603
C10: 1e-08; C0603
C11, C18: 1e-06; C0603
C12, C13: 1e-11; C0402
C14, C15, C16, C17, C23: 1e-07; C0402
C19, C20, C26, C27: 1e-08; C0402
C21: 1e-05; C1206
C22: 1e-05; C1210
C24, C25: 0.0001; EXV-9H
F1: 240.0; L0603
J1: PJ-037B; PJ-037B_PACKAGE
R2, R19: 1000.0; R0603
R4: 4700.0; R0603
R6: 2200.0; R0603
R7, R8, R9, R10, R11, R12, R13, R14, R15, R20, R21: 10000.0; R0603
R16: 47.0; R0603
R17: 100000.0; R0603
R18: 2231.0; R0603
R22: 9100.0; R0603
R23: 680000.0; R0603
R24: 120000.0; R0603
U1: STM32L152QEH6; UFBGA132
U2: TST-110-05-T-D-RA
U3: TSC2013QRSARQ1; QFN65P400X400X100-17N
U4: HTSS-105-01-G-D
U5: 47590-0001; MICRO_USB_AB
U6: prtr5v0u2ax; SOT143B
U7: ABLS-25.000MHZ-B2F-T
U8: ASEK-32.768KHz-ECST; ASEK
U9: LP3878SDX-ADJ/NOPB; WSON-8
U10: TPS3895ADRYR; SON-6
U11: 4-1437565-2; SW_4-1437565-2
U12: Q65110A2395; LGM67K-G1J2-24-Z
U13, U14: nc7sz125m5x; NC7SZ125M5X
U15: Dummy; DUMMY_PACKAGE_139

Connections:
CLK_CRYSTAL_U1_F1: C12.1, U1.F1, U7.1
CLK_CRYSTAL_U1_G1: C13.1, U1.G1, U7.2
CLK_U1_D1: U1.D1, U8.3
GND: C1.2, C2.2, C3.2, C4.2, C5.2, C6.2, C7.2, C8.2, C9.2, C10.2, C11.2, C12.2, C13.2, C14.2, C15.2, C19.2, C20.2, C21.2, C22.2, C23.2, C24.2, C25.2, C26.2, C27.2, J1.2, R2.2, R7.2, R13.2, R19.2, R22.2, R24.2, U1.D3, U1.E3, U1.F2, U1.F6, U1.F7, U1.F11, U1.F12, U1.J1, U2.4, U2.6, U2.8, U2.10, U2.12, U2.14, U2.16, U2.18, U2.20, U3.17, U4.9, U5.5, U5.6, U5.7, U5.8, U5.9, U6.1, U8.2, U9.3, U9.PAD, U10.2, U12.C, U13.2, U13.3, U14.1, U14.3, U15.1
NET_U1_A4: R7.1, U1.A4
NET_U1_B3: R6.1, U1.B3, U3.1
NET_U1_E2: C9.1, U1.E2
NET_U1_H2: R4.1, U1.H2, U14.4
NET_U1_M1: C10.1, C11.1, F1.1, U1.L1, U1.M1
NET_U1_M12: U11.3, U11.4
NET_U2_19: R13.1, U2.19
NET_U3_4: R15.1, U3.4
NET_U3_5: R14.1, U3.5
NET_U3_9: C16.2, C17.2, C18.2, R16.2, U3.9
NET_U3_15: R16.1, U3.8, U3.15
NET_U4_3: U3.12, U4.3
NET_U4_4: U3.14, U4.4
NET_U4_5: U3.11, U4.5
NET_U4_6: U3.13, U4.6
NET_U6_4: U5.1, U6.4
NET_U9_1: C20.1, U9.1
NET_U9_6: R18.2, R19.1, U9.6
NET_U9_8: R17.1, U9.8
NET_U10_1: R21.1, R22.1, U10.1
NET_U10_3: R23.2, R24.1, U10.3
NET_U10_4: R20.1, U10.4, U13.4, U14.2
NET_U11_1: R2.1, U11.1, U11.2
PROC_DAC_OUT2: U1.K4, U15.2
PROC_SYS_JTCK_SWCLK: R11.1, U1.A10, U2.9
PROC_SYS_JTDI: R9.1, U1.A9, U2.5
PROC_SYS_JTDO_TRACESWO: U1.A8, U2.13
PROC_SYS_JTMS_SWDIO: R10.1, U1.A11, U2.7
PROC_SYS_JTRST: R8.1, U1.A7, U2.3
PROC_USB_DM: U1.B12, U5.2, U6.3
PROC_USB_DP: U1.A12, U5.3, U6.2
RST_OUT_U2_SRESET_B: R12.1, U2.15, U13.1
VCC_S1_7V4: C21.1, C24.1, C25.1, J1.1, R17.2, U9.4
VCC_TIER1_3V3: C1.1, C2.1, C3.1, C4.1, C5.1, C6.1, C7.1, C8.1, C14.1, C15.1, C16.1, C17.1, C18.1, C19.1, C22.1, C23.1, C26.1, C27.1, F1.2, R4.2, R6.2, R8.2, R9.2, R10.2, R11.2, R12.2, R14.2, R15.2, R18.1, R20.2, R21.2, R23.1, U1.C4, U1.G2, U1.G6, U1.G7, U1.G11, U1.G12, U1.H3, U2.1, U2.2, U3.7, U3.10, U8.4, U9.5, U10.6, U13.5, U14.5

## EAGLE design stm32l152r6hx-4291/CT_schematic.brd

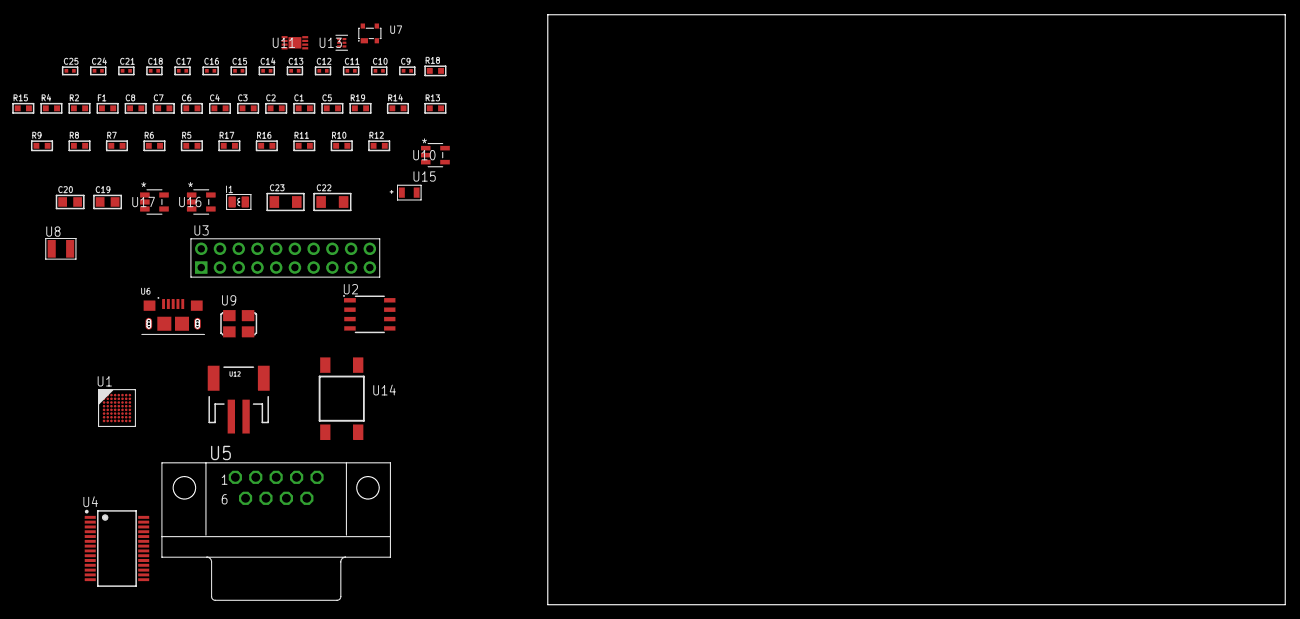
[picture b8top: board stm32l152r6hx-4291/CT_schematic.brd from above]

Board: 2 copper layers, 61 parts (0 on the bottom side), 48 nets, no tracks yet.

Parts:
C1, C2, C3, C4, C6: 1e-07; C0603
C5: 4.7e-06; C0603
C7: 1e-08; C0603
C8: 1e-06; C0603
C9, C10: 1e-11; C0402
C11, C18, C24, C25: 1e-08; C0402
C12, C13, C14, C15, C16, C17, C21: 1e-07; C0402
C19, C20: 1e-05; C0805
C22, C23: 1e-05; C1206
F1: 240.0; L0603
I1: 3.3e-06; L0806
R2: 1000.0; R0603
R4: 4700.0; R0603
R5, R6, R7, R8, R9, R13, R14, R19: 10000.0; R0603
R10: 100000.0; R0603
R11: 220000.0; R0603
R12: 1000000.0; R0603
R15: 9100.0; R0603
R16: 680000.0; R0603
R17: 120000.0; R0603
R18: 2000.0; R0603
U1: STM32L152R6H6; TFBGA64
U2: AT25256B-SSHL-T; SOIC-8
U3: TST-110-05-T-D-RA
U4: ST3241EBPR; SSOP-28
U5: 182-009-113R531; 182-009-MALE
U6: 10118193-0001LF; FCI_10118193-0001LF
U7: prtr5v0u2ax; SOT143B
U8: ABS07-32.768KHZ-7-T
U9: ASFL1-25MHZ-NCS; ASFL1
U10: ltc3406es5; TSOT-23-5
U11: MCP73831T-2ACI/MC; DFN8_2X3MC
U12: S2B-PH-SM4-TB(LF)(SN); JST-2-SMD
U13: TPS3895ADRYR; SON-6
U14: 4-1437565-2; SW_4-1437565-2
U15: Q65110A2395; LGM67K-G1J2-24-Z
U16, U17: nc7sz125m5x; NC7SZ125M5X

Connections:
CLK_CRYSTAL_U1_A1: C9.1, U1.A1, U8.1
CLK_CRYSTAL_U1_B1: C10.1, U1.B1, U8.2
CLK_U1_C1: U1.C1, U9.3
GND: C1.2, C2.2, C3.2, C4.2, C5.2, C6.2, C7.2, C8.2, C9.2, C10.2, C11.2, C12.2, C13.2, C16.2, C17.2, C18.2, C19.2, C20.1, C20.2, C21.2, C22.2, C23.2, C24.2, C25.2, R2.2, R5.2, R11.2, R15.2, R17.2, R18.2, U1.C2, U1.D4, U1.D5, U1.D6, U1.F1, U2.4, U3.4, U3.6, U3.8, U3.10, U3.12, U3.14, U3.16, U3.18, U3.20, U4.23, U4.25, U5.5, U6.5, U6.6, U6.7, U6.8, U6.9, U7.1, U9.2, U10.2, U11.6, U11.9, U12.2, U13.2, U15.C, U16.2, U16.3, U17.1, U17.3
INPUT_USBPOWER_5V: C22.1, R19.2, U6.1, U7.4, U11.1, U11.2
NET_U1_B2: C6.1, U1.B2
NET_U1_B4: R5.1, U1.B4
NET_U1_E1: R4.1, U1.E1, U17.4
NET_U1_H1: C7.1, C8.1, F1.1, U1.G1, U1.H1
NET_U1_H8: U14.3, U14.4
NET_U2_3: R6.1, U2.3
NET_U2_7: R8.1, U2.7
NET_U4_1: C15.1, U4.1
NET_U4_2: C15.2, U4.2
NET_U4_3: C17.1, U4.3
NET_U4_22: R10.1, U4.22
NET_U4_24: C14.2, U4.24
NET_U4_27: C16.1, U4.27
NET_U4_28: C14.1, U4.28
NET_U5_2: U4.4, U5.2
NET_U5_3: U4.9, U5.3
NET_U5_7: U4.5, U5.7
NET_U5_8: U4.10, U5.8
NET_U10_3: I1.1, U10.3
NET_U10_5: R11.1, R12.1, U10.5
NET_U10_ATNET_3: I1.2, R12.2
NET_U11_5: R19.1, U11.5
NET_U11_8: R18.1, U11.8
NET_U13_1: R14.1, R15.1, U13.1
NET_U13_3: R16.2, R17.1, U13.3
NET_U13_4: R13.1, U13.4, U16.4, U17.2
NET_U14_1: R2.1, U14.1, U14.2
PROC_SPI1_MISO: U1.A4, U2.2
PROC_SPI1_MOSI: U1.C4, U2.5
PROC_SPI1_NSS: R7.1, U1.A6, U2.1
PROC_SPI1_SCK: U1.F4, U2.6
PROC_SYS_JTCK_SWCLK: U1.A7, U3.9
PROC_SYS_JTDO_TRACESWO: U1.A5, U3.13
PROC_SYS_JTMS_SWDIO: U1.A8, U3.7
PROC_USART2_CTS: U1.G2, U4.13
PROC_USART2_RTS: U1.H2, U4.18
PROC_USART2_RX: U1.G3, U4.19
PROC_USART2_TX: U1.F3, U4.14
PROC_USB_DM: U1.C8, U6.2, U7.3
PROC_USB_DP: U1.B8, U6.3, U7.2
RST_OUT_U3_SRESET_B: R9.1, U3.15, U16.1
VCC_S1_3V7: C19.1, C23.1, U10.4, U11.3, U11.4, U12.1
VCC_TIER1_3V3: C1.1, C2.1, C3.1, C4.1, C5.1, C11.1, C12.1, C13.1, C18.1, C20.2, C21.1, C24.1, C25.1, F1.2, I1.2, R4.2, R6.2, R7.2, R8.2, R9.2, R10.2, R12.2, R13.2, R14.2, R16.1, U1.D2, U1.E4, U1.E5, U1.E6, U2.8, U3.1, U4.26, U9.4, U13.6, U16.5, U17.5
